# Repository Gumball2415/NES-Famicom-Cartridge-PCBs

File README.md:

# NES-Famicom-Cartridge-PCBs

 this is where i make the famicom cartridge PCBs
 
 All cartridge PCBs are licenced under the TAPR Open Hardware License.
 All software tools distributed with each project are licensed under the MIT-0 License.
 
 ## Support

If you enjoy this project or find it helpful, please support me on [Ko-Fi](https://ko-fi.com/persune) or [Patreon](https://www.patreon.com/persune)!

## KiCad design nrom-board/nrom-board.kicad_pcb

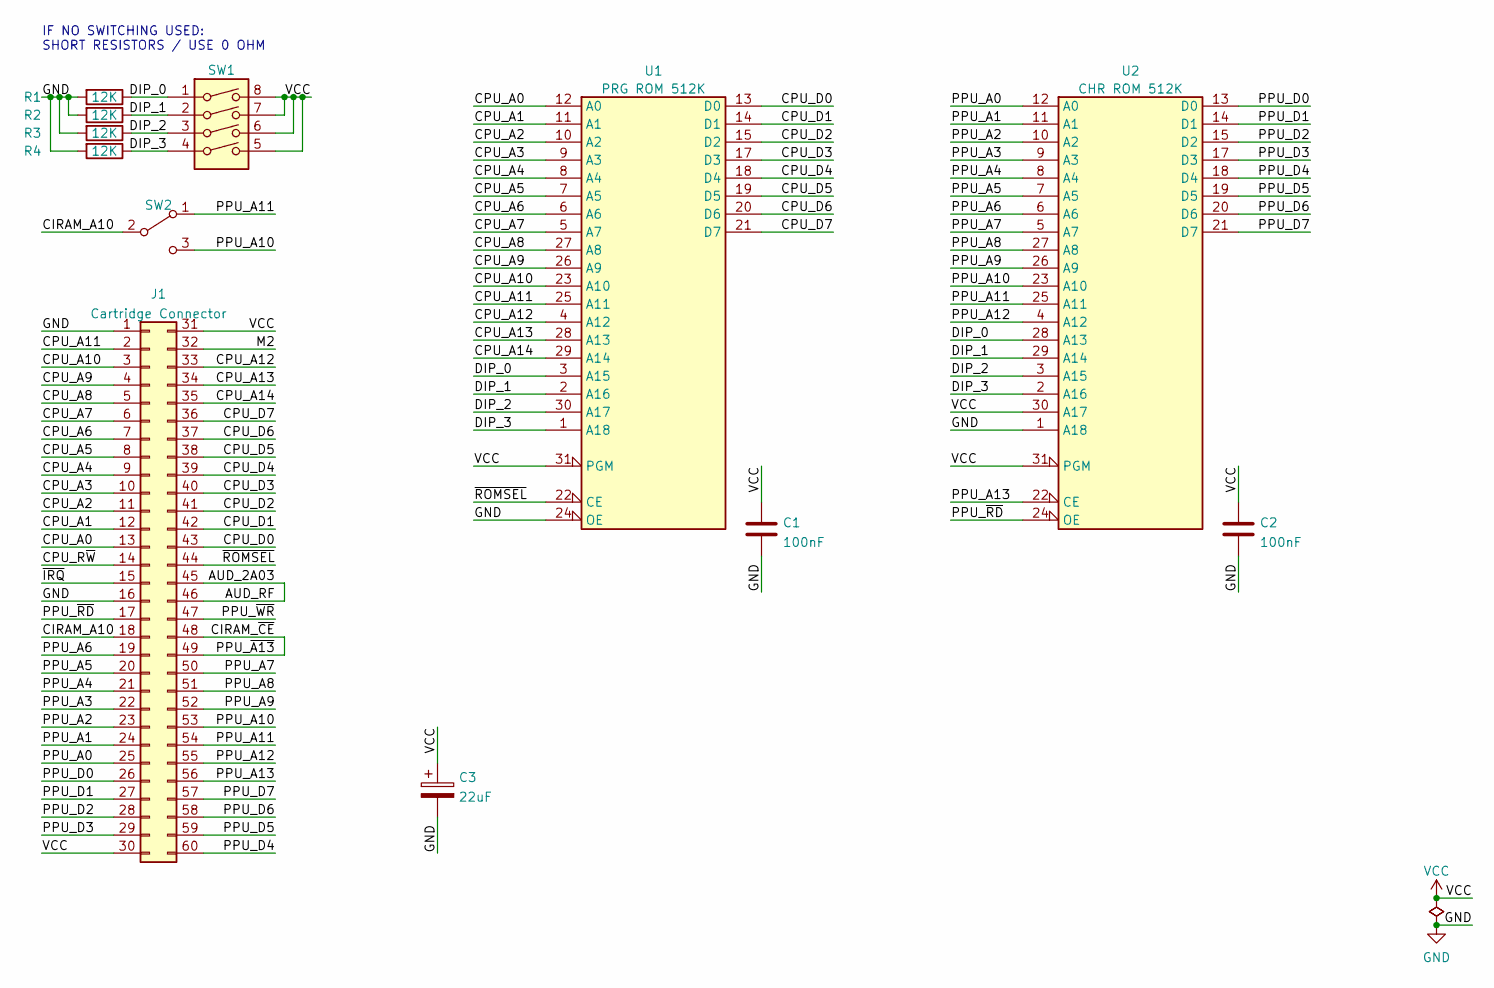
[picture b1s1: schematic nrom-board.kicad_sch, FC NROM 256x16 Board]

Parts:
C1, C2: 100nF; C_Disc-0805_D3.0mm_W1.6mm_P2.50mm
C3: 22uF; CP_Radial_D4.0mm_P2.00mm
J1: Cartridge Connector; HVC-TGROM-01
R1, R2, R3, R4: 12K; R_0805_2012Metric
SW1: SW_DIP_x04; DS04-254-2-04BK-SMT-ND
SW2: SW_SPDT; JS102011SCQN
U1: PRG ROM 512K; DIP-32_W15.24mm
U2: CHR ROM 512K; DIP-32_W15.24mm

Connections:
/AUD_2A03: J1.45, J1.46
/CIRAM_A10: J1.18, SW2.2 (B)
/CIRAM_~CE: J1.48, J1.49
/CPU_A0: J1.13, U1.12 (A0)
/CPU_A1: J1.12, U1.11 (A1)
/CPU_A2: J1.11, U1.10 (A2)
/CPU_A3: J1.10, U1.9 (A3)
/CPU_A4: J1.9, U1.8 (A4)
/CPU_A5: J1.8, U1.7 (A5)
/CPU_A6: J1.7, U1.6 (A6)
/CPU_A7: J1.6, U1.5 (A7)
/CPU_A8: J1.5, U1.27 (A8)
/CPU_A9: J1.4, U1.26 (A9)
/CPU_A10: J1.3, U1.23 (A10)
/CPU_A11: J1.2, U1.25 (A11)
/CPU_A12: J1.33, U1.4 (A12)
/CPU_A13: J1.34, U1.28 (A13)
/CPU_A14: J1.35, U1.29 (A14)
/CPU_D0: J1.43, U1.13 (D0)
/CPU_D1: J1.42, U1.14 (D1)
/CPU_D2: J1.41, U1.15 (D2)
/CPU_D3: J1.40, U1.17 (D3)
/CPU_D4: J1.39, U1.18 (D4)
/CPU_D5: J1.38, U1.19 (D5)
/CPU_D6: J1.37, U1.20 (D6)
/CPU_D7: J1.36, U1.21 (D7)
/CPU_R~W: J1.14
/DIP_0: R1.1, SW1.1, U1.3 (A15), U2.28 (A13)
/DIP_1: R2.1, SW1.2, U1.2 (A16), U2.29 (A14)
/DIP_2: R3.1, SW1.3, U1.30 (A17), U2.3 (A15)
/DIP_3: R4.1, SW1.4, U1.1 (A18), U2.2 (A16)
/M2: J1.32
/PPU_A0: J1.25, U2.12 (A0)
/PPU_A1: J1.24, U2.11 (A1)
/PPU_A2: J1.23, U2.10 (A2)
/PPU_A3: J1.22, U2.9 (A3)
/PPU_A4: J1.21, U2.8 (A4)
/PPU_A5: J1.20, U2.7 (A5)
/PPU_A6: J1.19, U2.6 (A6)
/PPU_A7: J1.50, U2.5 (A7)
/PPU_A8: J1.51, U2.27 (A8)
/PPU_A9: J1.52, U2.26 (A9)
/PPU_A10: J1.53, SW2.3 (C), U2.23 (A10)
/PPU_A11: J1.54, SW2.1 (A), U2.25 (A11)
/PPU_A12: J1.55, U2.4 (A12)
/PPU_A13: J1.56, U2.22 (CE)
/PPU_D0: J1.26, U2.13 (D0)
/PPU_D1: J1.27, U2.14 (D1)
/PPU_D2: J1.28, U2.15 (D2)
/PPU_D3: J1.29, U2.17 (D3)
/PPU_D4: J1.60, U2.18 (D4)
/PPU_D5: J1.59, U2.19 (D5)
/PPU_D6: J1.58, U2.20 (D6)
/PPU_D7: J1.57, U2.21 (D7)
/PPU_~RD: J1.17, U2.24 (OE)
/PPU_~WR: J1.47
/~IRQ: J1.15
/~ROMSEL: J1.44, U1.22 (CE)
GND: C1.2, C2.2, C3.2, J1.1, J1.16, R1.2, R2.2, R3.2, R4.2, U1.16 (GND), U1.24 (OE), U2.1 (A18), U2.16 (GND)
VCC: C1.1, C2.1, C3.1, J1.30, J1.31, SW1.5, SW1.6, SW1.7, SW1.8, U1.31 (PGM), U1.32 (VCC), U2.30 (A17), U2.31 (PGM), U2.32 (VCC)

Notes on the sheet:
IF NO SWITCHING USED: SHORT RESISTORS / USE 0 OHM

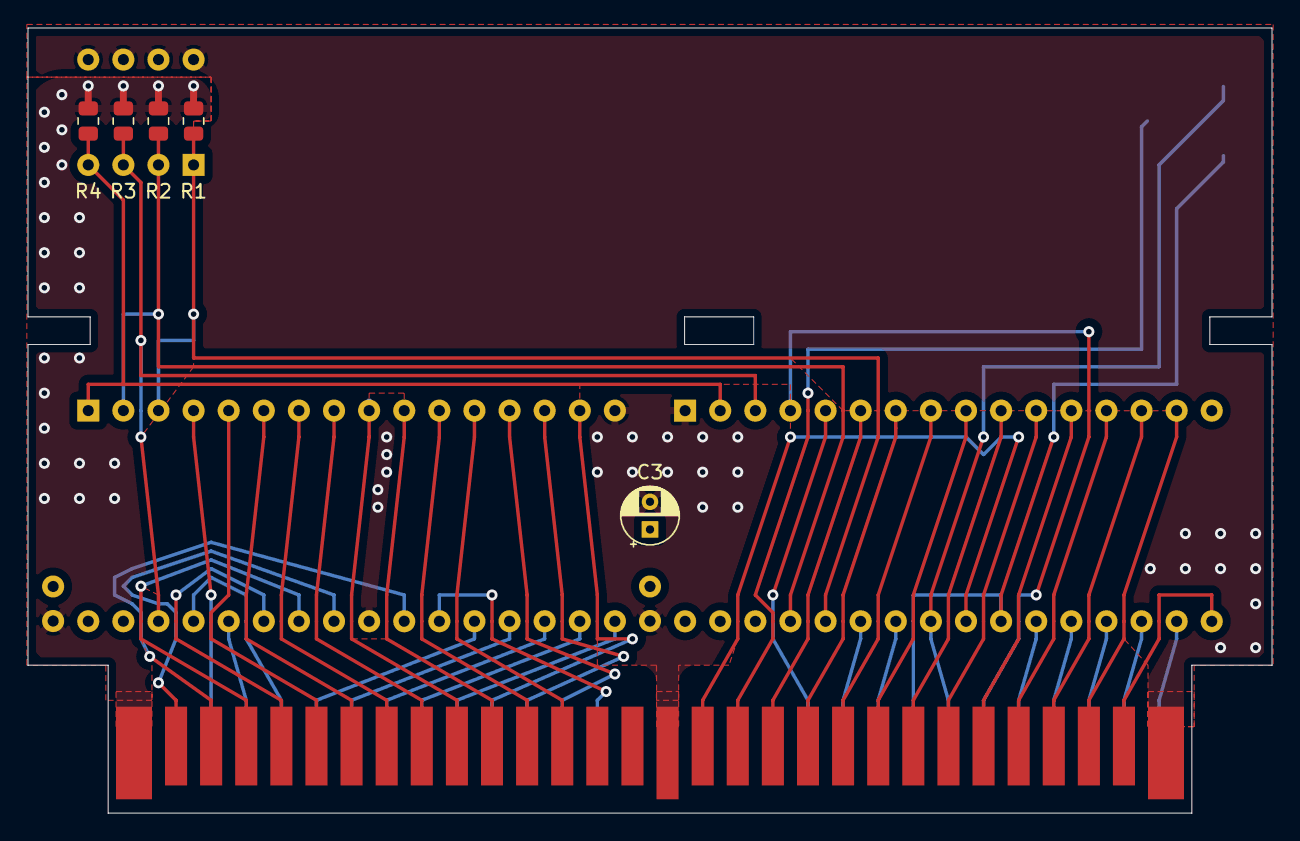
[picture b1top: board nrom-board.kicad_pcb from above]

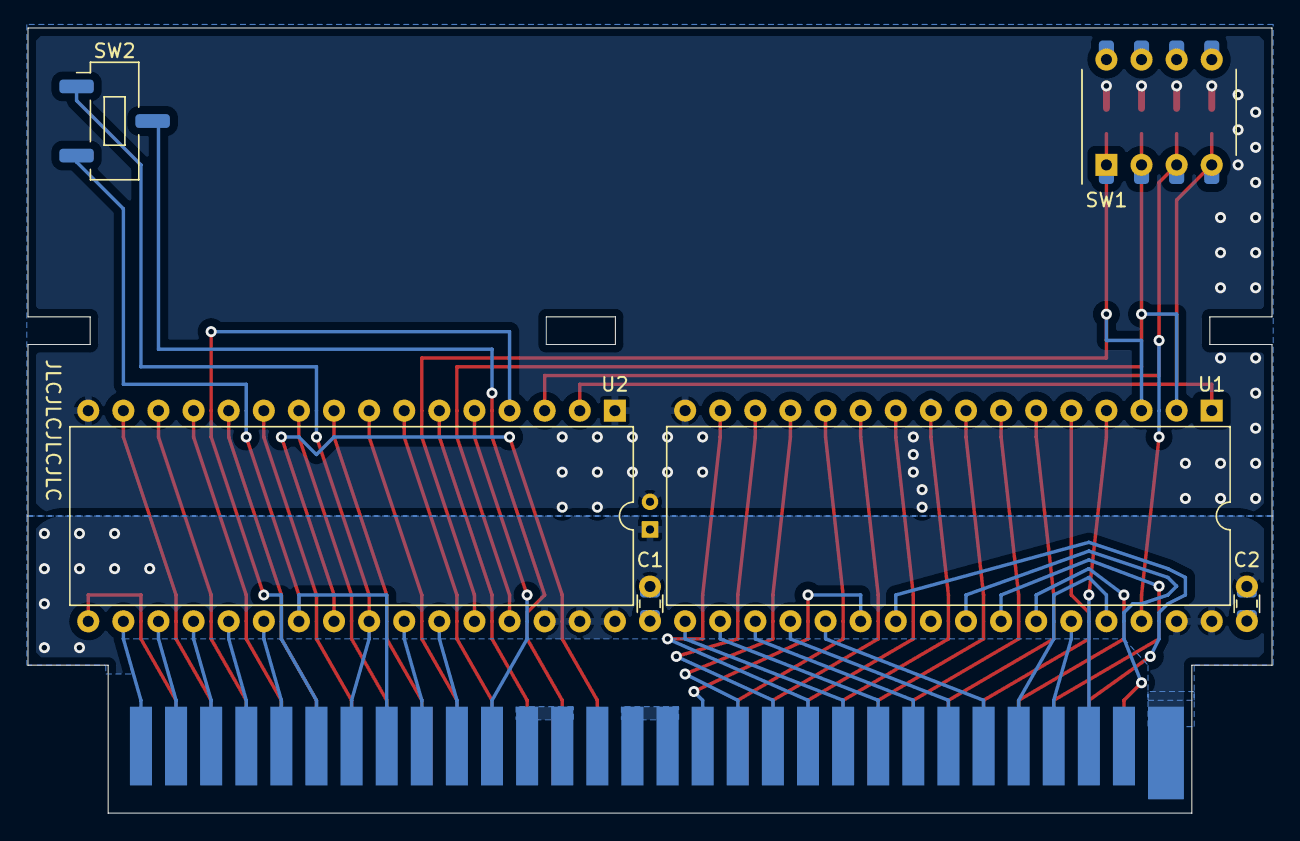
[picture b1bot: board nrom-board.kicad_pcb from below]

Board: 2 copper layers, 90.0 x 56.8 mm, 12 parts (6 on the bottom side), 56 nets.

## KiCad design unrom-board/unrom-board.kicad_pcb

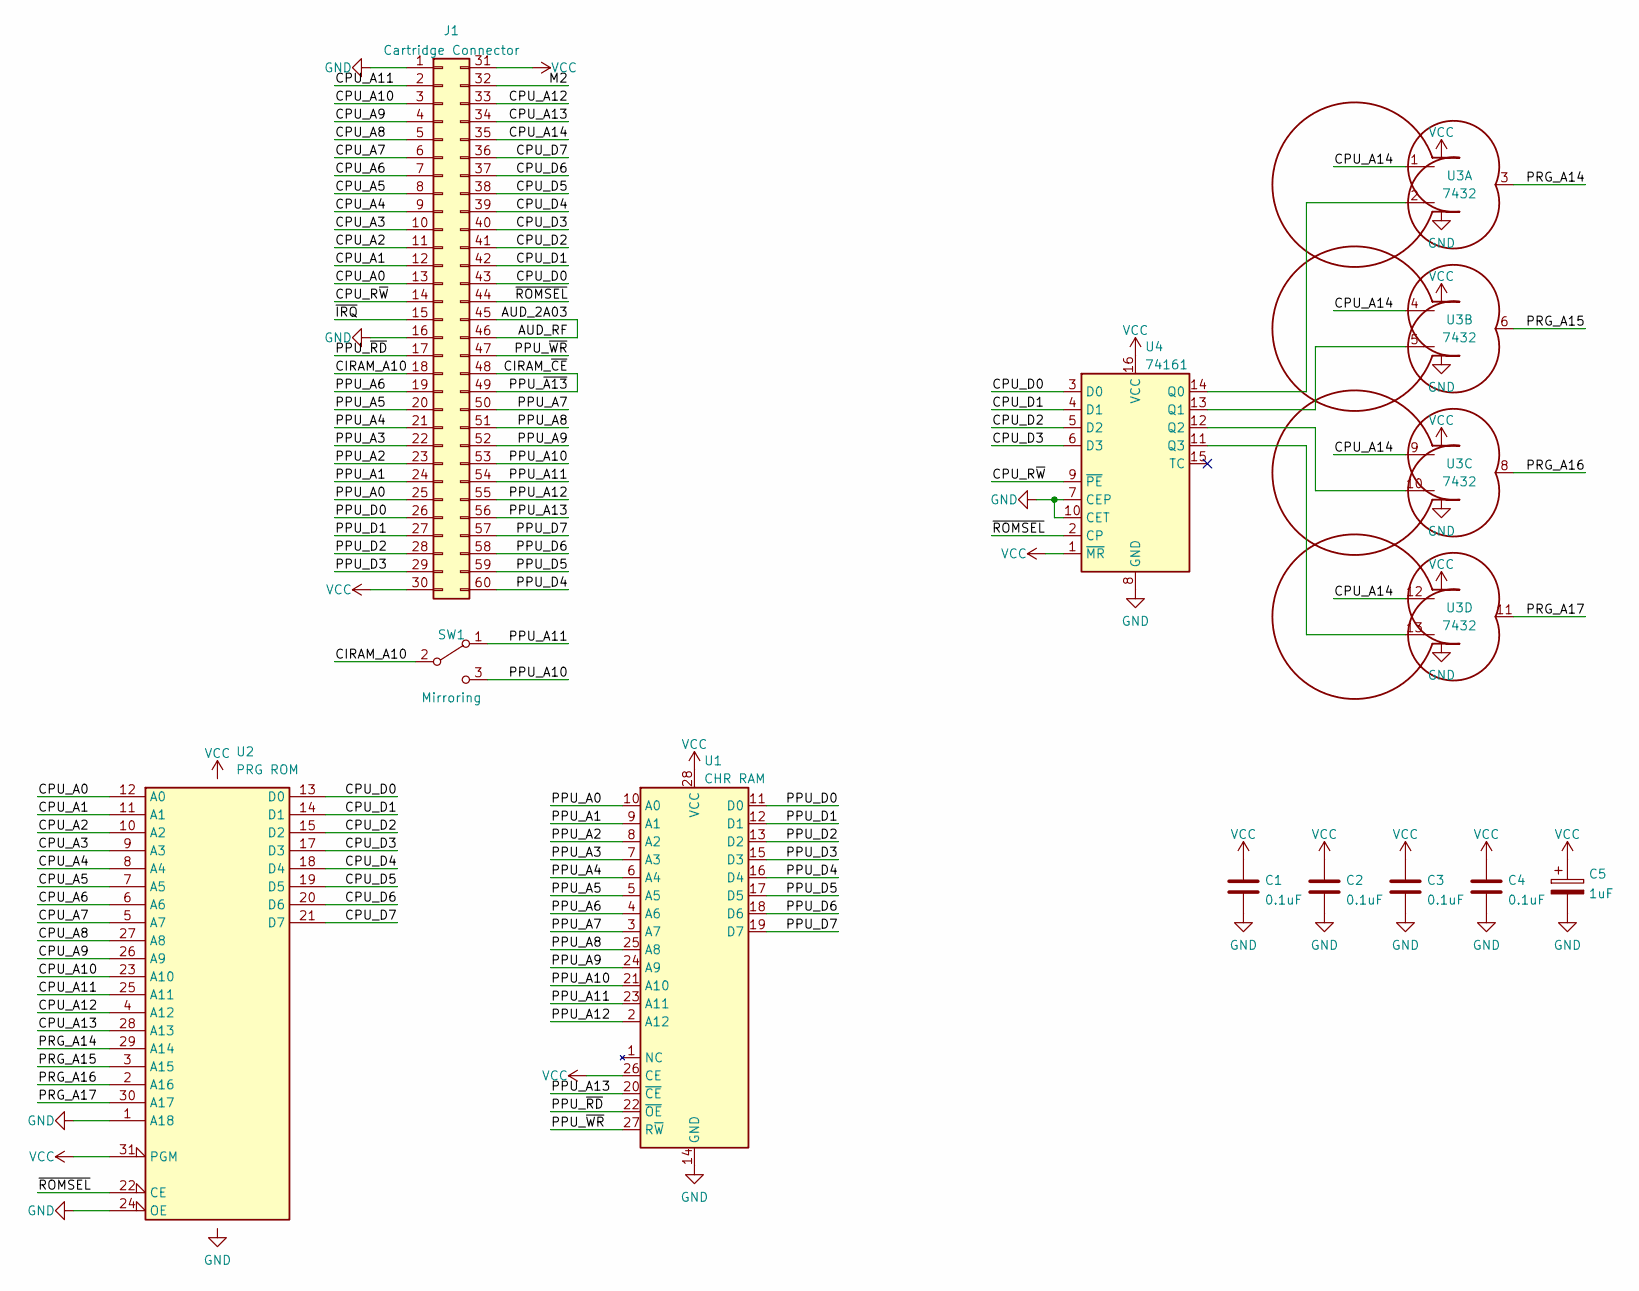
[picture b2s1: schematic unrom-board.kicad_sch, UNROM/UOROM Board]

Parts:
C1, C2, C3, C4: 0.1uF
C5: 1uF; CP_Radial_D4.0mm_P2.00mm
J1: Cartridge Connector
SW1: Mirroring
U1: CHR RAM; DIP-28_W15.24mm_Socket
U2: PRG ROM; DIP-32_W15.24mm_Socket
U3: 7432; DIP-14_W7.62mm
U4: 74161; DIP-16_W7.62mm

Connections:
/AUD_2A03: J1.45, J1.46
/CIRAM_A10: J1.18, SW1.2 (B)
/CIRAM_~CE: J1.48, J1.49
/CPU_A0: J1.13, U2.12 (A0)
/CPU_A1: J1.12, U2.11 (A1)
/CPU_A2: J1.11, U2.10 (A2)
/CPU_A3: J1.10, U2.9 (A3)
/CPU_A4: J1.9, U2.8 (A4)
/CPU_A5: J1.8, U2.7 (A5)
/CPU_A6: J1.7, U2.6 (A6)
/CPU_A7: J1.6, U2.5 (A7)
/CPU_A8: J1.5, U2.27 (A8)
/CPU_A9: J1.4, U2.26 (A9)
/CPU_A10: J1.3, U2.23 (A10)
/CPU_A11: J1.2, U2.25 (A11)
/CPU_A12: J1.33, U2.4 (A12)
/CPU_A13: J1.34, U2.28 (A13)
/CPU_A14: J1.35, U3.1, U3.4, U3.9, U3.12
/CPU_D0: J1.43, U2.13 (D0), U4.3 (D0)
/CPU_D1: J1.42, U2.14 (D1), U4.4 (D1)
/CPU_D2: J1.41, U2.15 (D2), U4.5 (D2)
/CPU_D3: J1.40, U2.17 (D3), U4.6 (D3)
/CPU_D4: J1.39, U2.18 (D4)
/CPU_D5: J1.38, U2.19 (D5)
/CPU_D6: J1.37, U2.20 (D6)
/CPU_D7: J1.36, U2.21 (D7)
/CPU_R~W: J1.14, U4.9 (~PE)
/M2: J1.32
/PPU_A0: J1.25, U1.10 (A0)
/PPU_A1: J1.24, U1.9 (A1)
/PPU_A2: J1.23, U1.8 (A2)
/PPU_A3: J1.22, U1.7 (A3)
/PPU_A4: J1.21, U1.6 (A4)
/PPU_A5: J1.20, U1.5 (A5)
/PPU_A6: J1.19, U1.4 (A6)
/PPU_A7: J1.50, U1.3 (A7)
/PPU_A8: J1.51, U1.25 (A8)
/PPU_A9: J1.52, U1.24 (A9)
/PPU_A10: J1.53, SW1.3 (C), U1.21 (A10)
/PPU_A11: J1.54, SW1.1 (A), U1.23 (A11)
/PPU_A12: J1.55, U1.2 (A12)
/PPU_A13: J1.56, U1.20 (~CE)
/PPU_D0: J1.26, U1.11 (D0)
/PPU_D1: J1.27, U1.12 (D1)
/PPU_D2: J1.28, U1.13 (D2)
/PPU_D3: J1.29, U1.15 (D3)
/PPU_D4: J1.60, U1.16 (D4)
/PPU_D5: J1.59, U1.17 (D5)
/PPU_D6: J1.58, U1.18 (D6)
/PPU_D7: J1.57, U1.19 (D7)
/PPU_~RD: J1.17, U1.22 (~OE)
/PPU_~WR: J1.47, U1.27 (R~W)
/PRG_A14: U2.29 (A14), U3.3
/PRG_A15: U2.3 (A15), U3.6
/PRG_A16: U2.2 (A16), U3.8
/PRG_A17: U2.30 (A17), U3.11
/~IRQ: J1.15
/~ROMSEL: J1.44, U2.22 (CE), U4.2 (CP)
GND: C1.2, C2.2, C3.2, C4.2, C5.2, J1.1, J1.16, U1.14 (GND), U2.1 (A18), U2.16 (GND), U2.24 (OE), U3.7 (GND), U4.7 (CEP), U4.8 (GND), U4.10 (CET)
unnamed: U3.2, U4.14 (Q0)
unnamed: U3.5, U4.13 (Q1)
unnamed: U3.10, U4.12 (Q2)
unnamed: U3.13, U4.11 (Q3)
VCC: C1.1, C2.1, C3.1, C4.1, C5.1, J1.30, J1.31, U1.26 (CE), U1.28 (VCC), U2.31 (PGM), U2.32 (VCC), U3.14 (VCC), U4.1 (~MR), U4.16 (VCC)

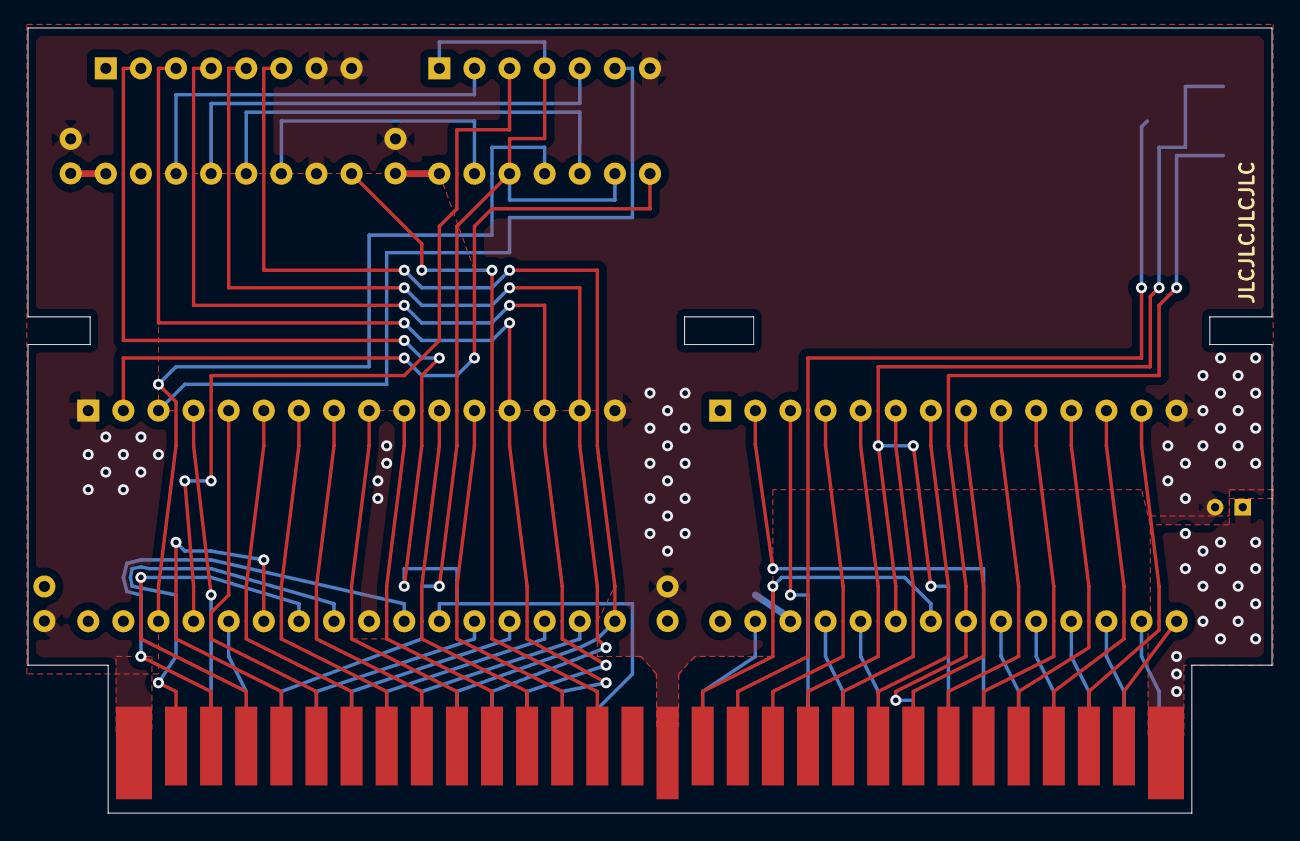
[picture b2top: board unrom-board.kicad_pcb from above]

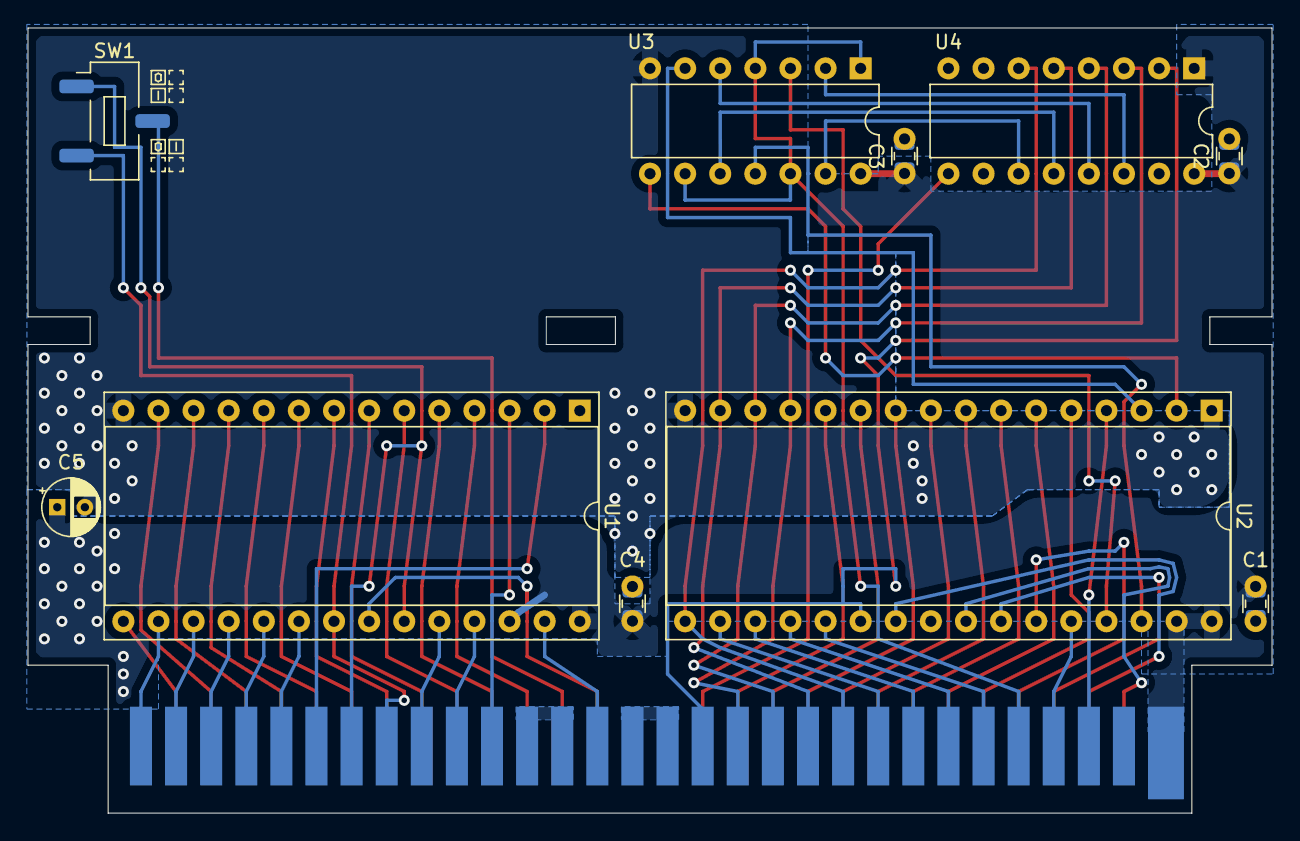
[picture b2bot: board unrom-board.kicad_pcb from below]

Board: 2 copper layers, 90.0 x 56.8 mm, 11 parts (10 on the bottom side), 62 nets.

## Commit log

2022-11-23 NROM x16: Initial commit
2022-11-23 UxROM 256K: Initial commit
2022-11-23 Add license
2022-11-25 NROM x16: Refactor ROM bankswitching circuit
    - Refactor routing
2022-11-25 Add image to readme
2022-11-30 Add FUNDING.yml
2023-01-21 NROM x16: add ROM packer
2023-04-05 Add support readme
